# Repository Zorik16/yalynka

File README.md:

# Ялинка — мультивібратор на BC547

**Автор:** Nesterov Maksym
**Курс:** Проєктна робота в СКБ «Sky» (осінь 2026)

Плата у формі ялинки: дві групи світлодіодів (по 3 шт.) блимають по черзі.
Схема: симетричний мультивібратор на двох транзисторах BC547, живлення 5 В від USB Type‑C.
Проєкт виконано в **KiCad 10**.

## Схема електрична принципова

Векторна версія: [schematic.svg](schematic.svg) · PDF: [schematic.pdf](schematic.pdf)

## Плата (3D)

## Як працює

- Q1, Q2 (BC547) по черзі відкриваються й закриваються. Час перемикання задають R9/R10 (22 кОм) і C1/C2 (100 мкФ), період ≈ 1.4·R·C ≈ 3 с.
- D1–D3 (через R1–R3, 330 Ом) світяться, коли відкритий Q1; D4–D6 (через R4–R6), коли відкритий Q2.
- J1 — USB Type‑C (тільки живлення), R7/R8 по 5.1 кОм на CC1/CC2, щоб зарядник видавав 5 В.

## Перелік елементів

| Позначення | Елемент | Кількість |
|---|---|---|
| Q1, Q2 | BC547 (TO‑92) | 2 |
| D1–D6 | LED 5 мм | 6 |
| R1–R6 | 330 Ом | 6 |
| R9, R10 | 22 кОм | 2 |
| R7, R8 | 5.1 кОм | 2 |
| C1, C2 | 100 мкФ, електролітичний | 2 |
| J1 | USB Type‑C, 6 pin (power only) | 1 |

## Файли

| Файл | Що це |
|---|---|
| `yalynka.kicad_pro` | проєкт KiCad |
| `yalynka.kicad_sch` | схема |
| `yalynka.kicad_pcb` | плата (100 × 120 мм, 2 шари) |
| `Yalynka.pretty/` | посадкове місце роз'єму USB‑C |
| `yalynka.step` | 3D-модель плати (для Fusion 360 / FreeCAD) |
| `yalynka_stand.stl` | підставка під плату (паз під «стовбур» ялинки) |

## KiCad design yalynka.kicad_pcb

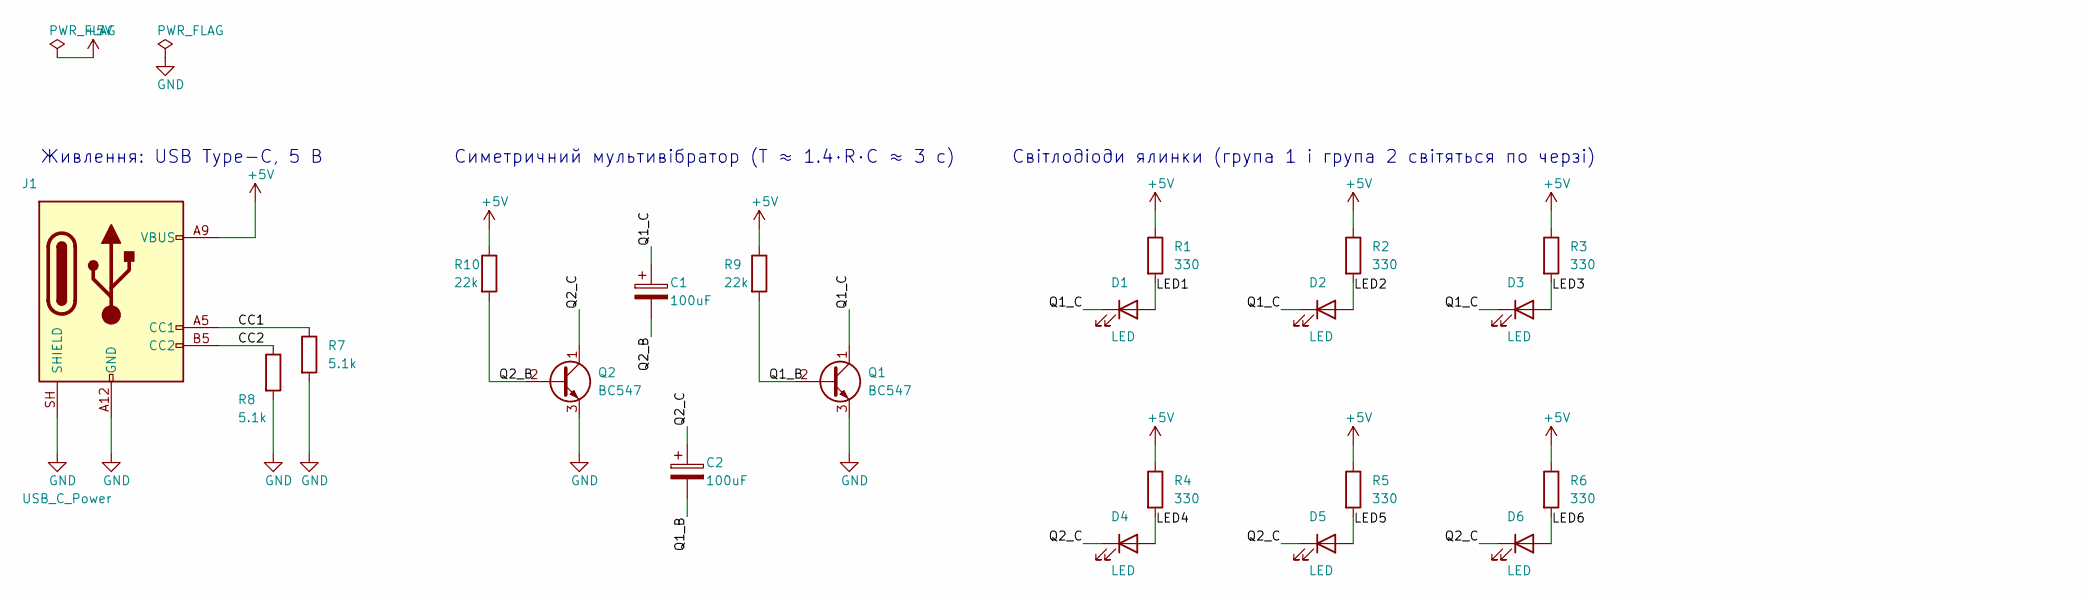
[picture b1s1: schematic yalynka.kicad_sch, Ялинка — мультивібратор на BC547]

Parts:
C1, C2: 100uF; CP_Radial_D5.0mm_P2.00mm
D1, D2, D3, D4, D5, D6: LED; LED_D5.0mm
J1: USB_C_Power; USB_C_Receptacle_PowerOnly_6P
Q1, Q2: BC547; TO-92_Inline
R1, R2, R3, R4, R5, R6: 330; R_Axial_DIN0207_L6.3mm_D2.5mm_P2.54mm_Vertical
R7, R8: 5.1k; R_Axial_DIN0207_L6.3mm_D2.5mm_P2.54mm_Vertical
R9, R10: 22k; R_Axial_DIN0207_L6.3mm_D2.5mm_P2.54mm_Vertical

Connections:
+5V: J1.A9 (VBUS), J1.B9 (VBUS), R1.1, R2.1, R3.1, R4.1, R5.1, R6.1, R9.1, R10.1
/CC1: J1.A5 (CC1), R7.1
/CC2: J1.B5 (CC2), R8.1
/LED1: D1.2 (A), R1.2
/LED2: D2.2 (A), R2.2
/LED3: D3.2 (A), R3.2
/LED4: D4.2 (A), R4.2
/LED5: D5.2 (A), R5.2
/LED6: D6.2 (A), R6.2
/Q1_B: C2.2, Q1.2 (B), R9.2
/Q1_C: C1.1, D1.1 (K), D2.1 (K), D3.1 (K), Q1.1 (C)
/Q2_B: C1.2, Q2.2 (B), R10.2
/Q2_C: C2.1, D4.1 (K), D5.1 (K), D6.1 (K), Q2.1 (C)
GND: J1.A12 (GND), J1.B12 (GND), J1.SH (SHIELD), Q1.3 (E), Q2.3 (E), R7.2, R8.2

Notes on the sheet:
Світлодіоди ялинки (група 1 і група 2 світяться по черзі)
Симетричний мультивібратор (T ≈ 1.4·R·C ≈ 3 с)
Живлення: USB Type-C, 5 В

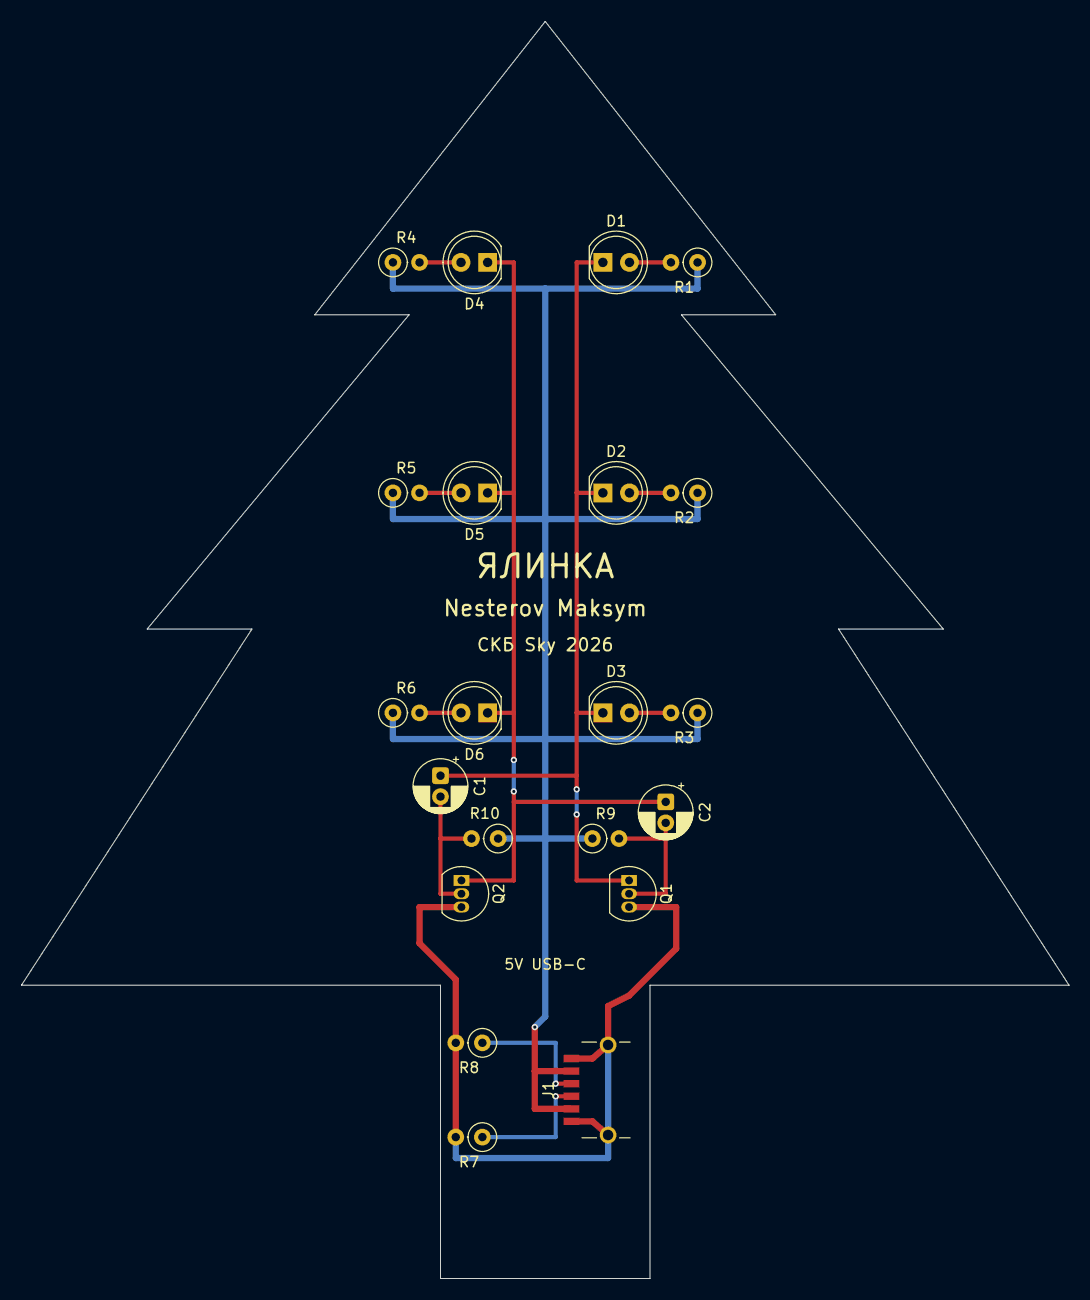
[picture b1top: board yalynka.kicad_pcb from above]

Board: 2 copper layers, 100.0 x 120.0 mm, 21 parts (0 on the bottom side), 14 nets.
